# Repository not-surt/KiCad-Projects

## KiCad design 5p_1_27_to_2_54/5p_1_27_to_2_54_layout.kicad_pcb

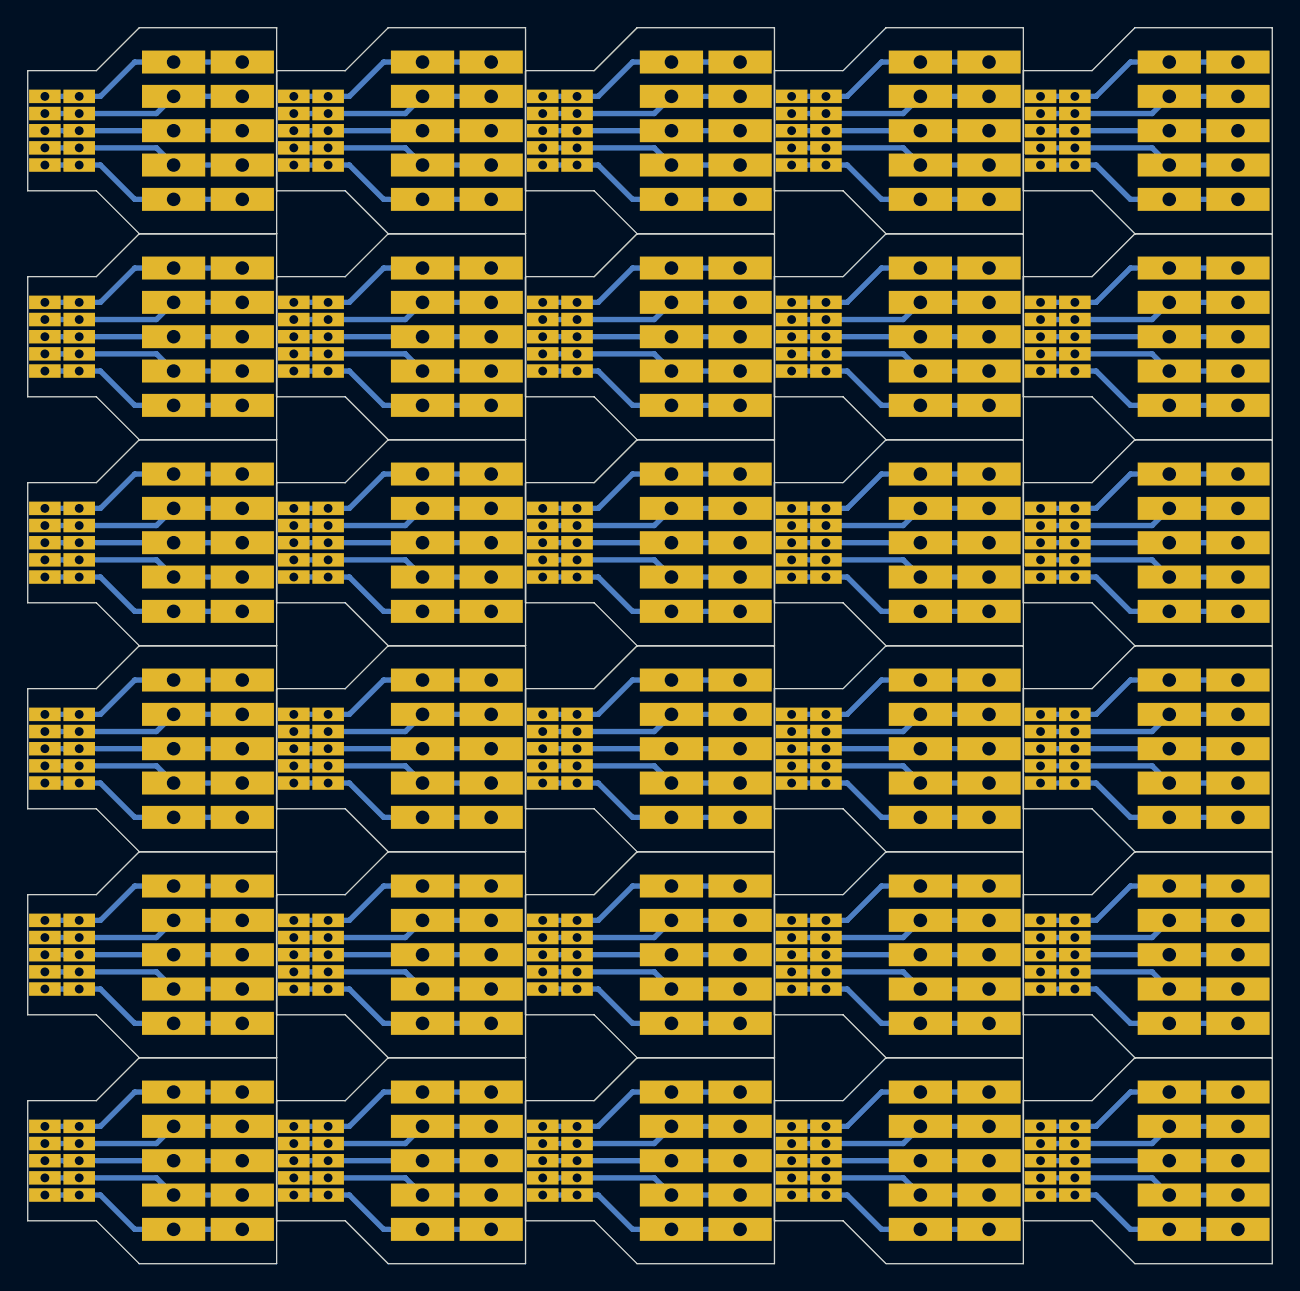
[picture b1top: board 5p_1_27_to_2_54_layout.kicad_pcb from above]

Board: 2 copper layers, 92.1 x 91.4 mm, 120 parts (0 on the bottom side), 5 nets.

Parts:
J1, J2, J5, J6, J9, J10, J13, J14, J17, J18, J21, J22, J25, J26, J29, J30, J33, J34, J37, J38, J41, J42, J45, J46, J49, J50, J53, J54, J57, J58, J61, J62, J65, J66, J69, J70, J73, J74, J77, J78, J81, J82, J85, J86, J89, J90, J93, J94, J97, J98, J101, J102, J105, J106, J109, J110, J113, J114, J117, J118: Conn_01x05; PinHeader_1x05_P1.27mm_Vertical_stretch
J3, J4, J7, J8, J11, J12, J15, J16, J19, J20, J23, J24, J27, J28, J31, J32, J35, J36, J39, J40, J43, J44, J47, J48, J51, J52, J55, J56, J59, J60, J63, J64, J67, J68, J71, J72, J75, J76, J79, J80, J83, J84, J87, J88, J91, J92, J95, J96, J99, J100, J103, J104, J107, J108, J111, J112, J115, J116, J119, J120: Conn_01x05; PinHeader_1x05_P2.54mm_Vertical_stretch

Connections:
unnamed: J1.1, J2.1, J3.1, J4.1, J5.1, J6.1, J7.1, J8.1, J9.1, J10.1, J11.1, J12.1, J13.1, J14.1, J15.1, J16.1, J17.1, J18.1, J19.1, J20.1, J21.1, J22.1, J23.1, J24.1, J25.1, J26.1, J27.1, J28.1, J29.1, J30.1, J31.1, J32.1, J33.1, J34.1, J35.1, J36.1, J37.1, J38.1, J39.1, J40.1, J41.1, J42.1, J43.1, J44.1, J45.1, J46.1, J47.1, J48.1, J49.1, J50.1, J51.1, J52.1, J53.1, J54.1, J55.1, J56.1, J57.1, J58.1, J59.1, J60.1, J61.1, J62.1, J63.1, J64.1, J65.1, J66.1, J67.1, J68.1, J69.1, J70.1, J71.1, J72.1, J73.1, J74.1, J75.1, J76.1, J77.1, J78.1, J79.1, J80.1, J81.1, J82.1, J83.1, J84.1, J85.1, J86.1, J87.1, J88.1, J89.1, J90.1, J91.1, J92.1, J93.1, J94.1, J95.1, J96.1, J97.1, J98.1, J99.1, J100.1, J101.1, J102.1, J103.1, J104.1, J105.1, J106.1, J107.1, J108.1, J109.1, J110.1, J111.1, J112.1, J113.1, J114.1, J115.1, J116.1, J117.1, J118.1, J119.1, J120.1
unnamed: J1.2, J2.2, J3.2, J4.2, J5.2, J6.2, J7.2, J8.2, J9.2, J10.2, J11.2, J12.2, J13.2, J14.2, J15.2, J16.2, J17.2, J18.2, J19.2, J20.2, J21.2, J22.2, J23.2, J24.2, J25.2, J26.2, J27.2, J28.2, J29.2, J30.2, J31.2, J32.2, J33.2, J34.2, J35.2, J36.2, J37.2, J38.2, J39.2, J40.2, J41.2, J42.2, J43.2, J44.2, J45.2, J46.2, J47.2, J48.2, J49.2, J50.2, J51.2, J52.2, J53.2, J54.2, J55.2, J56.2, J57.2, J58.2, J59.2, J60.2, J61.2, J62.2, J63.2, J64.2, J65.2, J66.2, J67.2, J68.2, J69.2, J70.2, J71.2, J72.2, J73.2, J74.2, J75.2, J76.2, J77.2, J78.2, J79.2, J80.2, J81.2, J82.2, J83.2, J84.2, J85.2, J86.2, J87.2, J88.2, J89.2, J90.2, J91.2, J92.2, J93.2, J94.2, J95.2, J96.2, J97.2, J98.2, J99.2, J100.2, J101.2, J102.2, J103.2, J104.2, J105.2, J106.2, J107.2, J108.2, J109.2, J110.2, J111.2, J112.2, J113.2, J114.2, J115.2, J116.2, J117.2, J118.2, J119.2, J120.2
unnamed: J1.3, J2.3, J3.3, J4.3, J5.3, J6.3, J7.3, J8.3, J9.3, J10.3, J11.3, J12.3, J13.3, J14.3, J15.3, J16.3, J17.3, J18.3, J19.3, J20.3, J21.3, J22.3, J23.3, J24.3, J25.3, J26.3, J27.3, J28.3, J29.3, J30.3, J31.3, J32.3, J33.3, J34.3, J35.3, J36.3, J37.3, J38.3, J39.3, J40.3, J41.3, J42.3, J43.3, J44.3, J45.3, J46.3, J47.3, J48.3, J49.3, J50.3, J51.3, J52.3, J53.3, J54.3, J55.3, J56.3, J57.3, J58.3, J59.3, J60.3, J61.3, J62.3, J63.3, J64.3, J65.3, J66.3, J67.3, J68.3, J69.3, J70.3, J71.3, J72.3, J73.3, J74.3, J75.3, J76.3, J77.3, J78.3, J79.3, J80.3, J81.3, J82.3, J83.3, J84.3, J85.3, J86.3, J87.3, J88.3, J89.3, J90.3, J91.3, J92.3, J93.3, J94.3, J95.3, J96.3, J97.3, J98.3, J99.3, J100.3, J101.3, J102.3, J103.3, J104.3, J105.3, J106.3, J107.3, J108.3, J109.3, J110.3, J111.3, J112.3, J113.3, J114.3, J115.3, J116.3, J117.3, J118.3, J119.3, J120.3
unnamed: J1.4, J2.4, J3.4, J4.4, J5.4, J6.4, J7.4, J8.4, J9.4, J10.4, J11.4, J12.4, J13.4, J14.4, J15.4, J16.4, J17.4, J18.4, J19.4, J20.4, J21.4, J22.4, J23.4, J24.4, J25.4, J26.4, J27.4, J28.4, J29.4, J30.4, J31.4, J32.4, J33.4, J34.4, J35.4, J36.4, J37.4, J38.4, J39.4, J40.4, J41.4, J42.4, J43.4, J44.4, J45.4, J46.4, J47.4, J48.4, J49.4, J50.4, J51.4, J52.4, J53.4, J54.4, J55.4, J56.4, J57.4, J58.4, J59.4, J60.4, J61.4, J62.4, J63.4, J64.4, J65.4, J66.4, J67.4, J68.4, J69.4, J70.4, J71.4, J72.4, J73.4, J74.4, J75.4, J76.4, J77.4, J78.4, J79.4, J80.4, J81.4, J82.4, J83.4, J84.4, J85.4, J86.4, J87.4, J88.4, J89.4, J90.4, J91.4, J92.4, J93.4, J94.4, J95.4, J96.4, J97.4, J98.4, J99.4, J100.4, J101.4, J102.4, J103.4, J104.4, J105.4, J106.4, J107.4, J108.4, J109.4, J110.4, J111.4, J112.4, J113.4, J114.4, J115.4, J116.4, J117.4, J118.4, J119.4, J120.4
unnamed: J1.5, J2.5, J3.5, J4.5, J5.5, J6.5, J7.5, J8.5, J9.5, J10.5, J11.5, J12.5, J13.5, J14.5, J15.5, J16.5, J17.5, J18.5, J19.5, J20.5, J21.5, J22.5, J23.5, J24.5, J25.5, J26.5, J27.5, J28.5, J29.5, J30.5, J31.5, J32.5, J33.5, J34.5, J35.5, J36.5, J37.5, J38.5, J39.5, J40.5, J41.5, J42.5, J43.5, J44.5, J45.5, J46.5, J47.5, J48.5, J49.5, J50.5, J51.5, J52.5, J53.5, J54.5, J55.5, J56.5, J57.5, J58.5, J59.5, J60.5, J61.5, J62.5, J63.5, J64.5, J65.5, J66.5, J67.5, J68.5, J69.5, J70.5, J71.5, J72.5, J73.5, J74.5, J75.5, J76.5, J77.5, J78.5, J79.5, J80.5, J81.5, J82.5, J83.5, J84.5, J85.5, J86.5, J87.5, J88.5, J89.5, J90.5, J91.5, J92.5, J93.5, J94.5, J95.5, J96.5, J97.5, J98.5, J99.5, J100.5, J101.5, J102.5, J103.5, J104.5, J105.5, J106.5, J107.5, J108.5, J109.5, J110.5, J111.5, J112.5, J113.5, J114.5, J115.5, J116.5, J117.5, J118.5, J119.5, J120.5

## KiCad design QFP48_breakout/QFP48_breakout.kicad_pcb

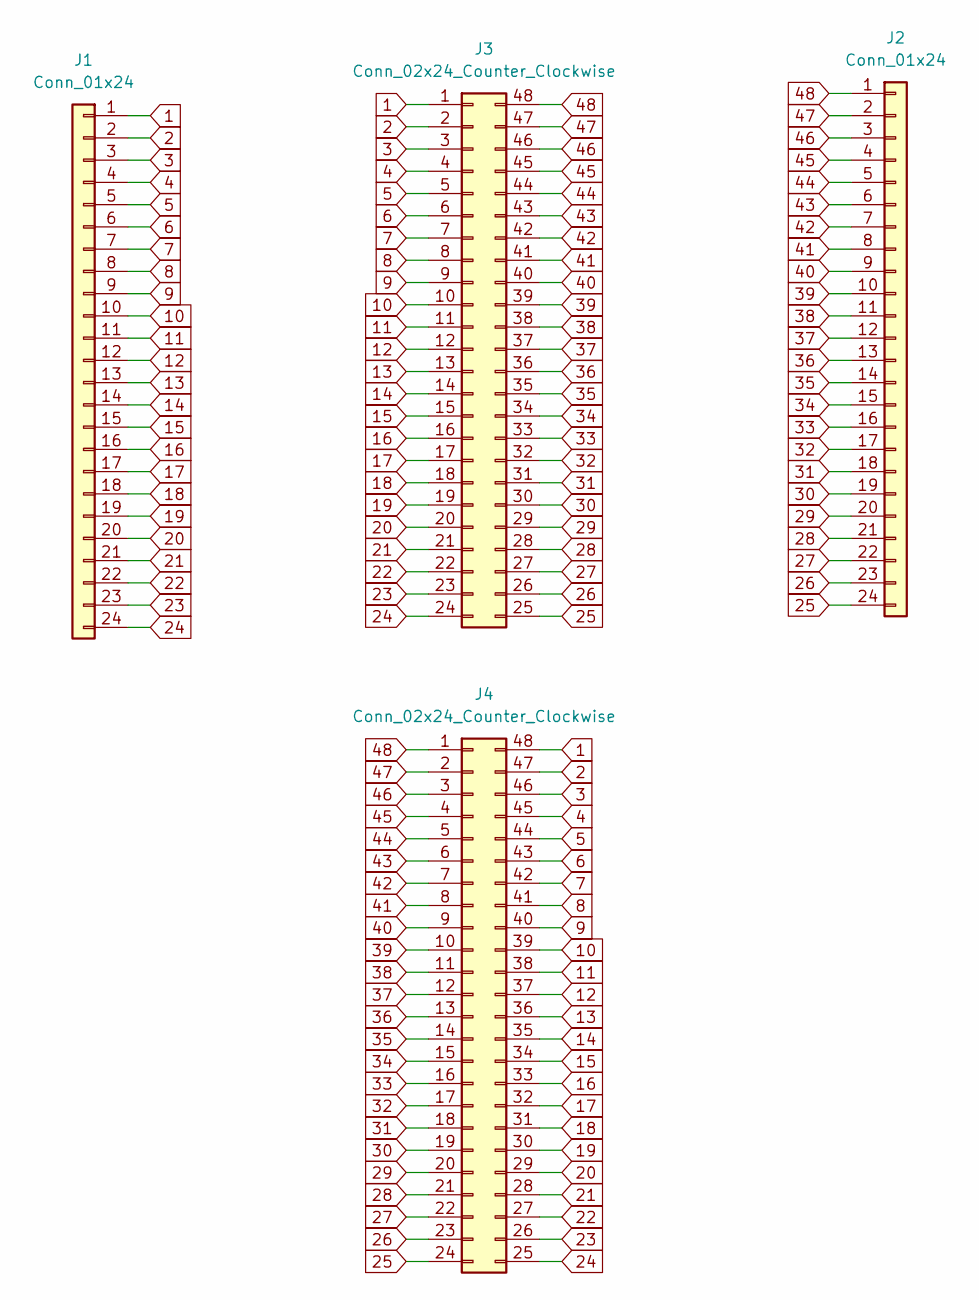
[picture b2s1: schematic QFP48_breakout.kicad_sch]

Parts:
J1, J2: Conn_01x24; PinHeader_1x24_P2.54mm_Vertical_no_silk
J3: Conn_02x24_Counter_Clockwise; LQFP-48-1EP_7x7mm_P0.5mm_EP3.6x3.6mm
J4: Conn_02x24_Counter_Clockwise; QFN-48-1EP_7x7mm_P0.5mm_EP5.15x5.15mm

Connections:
1: J1.1, J3.1, J4.48
2: J1.2, J3.2, J4.47
3: J1.3, J3.3, J4.46
4: J1.4, J3.4, J4.45
5: J1.5, J3.5, J4.44
6: J1.6, J3.6, J4.43
7: J1.7, J3.7, J4.42
8: J1.8, J3.8, J4.41
9: J1.9, J3.9, J4.40
10: J1.10, J3.10, J4.39
11: J1.11, J3.11, J4.38
12: J1.12, J3.12, J4.37
13: J1.13, J3.13, J4.36
14: J1.14, J3.14, J4.35
15: J1.15, J3.15, J4.34
16: J1.16, J3.16, J4.33
17: J1.17, J3.17, J4.32
18: J1.18, J3.18, J4.31
19: J1.19, J3.19, J4.30
20: J1.20, J3.20, J4.29
21: J1.21, J3.21, J4.28
22: J1.22, J3.22, J4.27
23: J1.23, J3.23, J4.26
24: J1.24, J3.24, J4.25
25: J2.24, J3.25, J4.24
26: J2.23, J3.26, J4.23
27: J2.22, J3.27, J4.22
28: J2.21, J3.28, J4.21
29: J2.20, J3.29, J4.20
30: J2.19, J3.30, J4.19
31: J2.18, J3.31, J4.18
32: J2.17, J3.32, J4.17
33: J2.16, J3.33, J4.16
34: J2.15, J3.34, J4.15
35: J2.14, J3.35, J4.14
36: J2.13, J3.36, J4.13
37: J2.12, J3.37, J4.12
38: J2.11, J3.38, J4.11
39: J2.10, J3.39, J4.10
40: J2.9, J3.40, J4.9
41: J2.8, J3.41, J4.8
42: J2.7, J3.42, J4.7
43: J2.6, J3.43, J4.6
44: J2.5, J3.44, J4.5
45: J2.4, J3.45, J4.4
46: J2.3, J3.46, J4.3
47: J2.2, J3.47, J4.2
48: J2.1, J3.48, J4.1

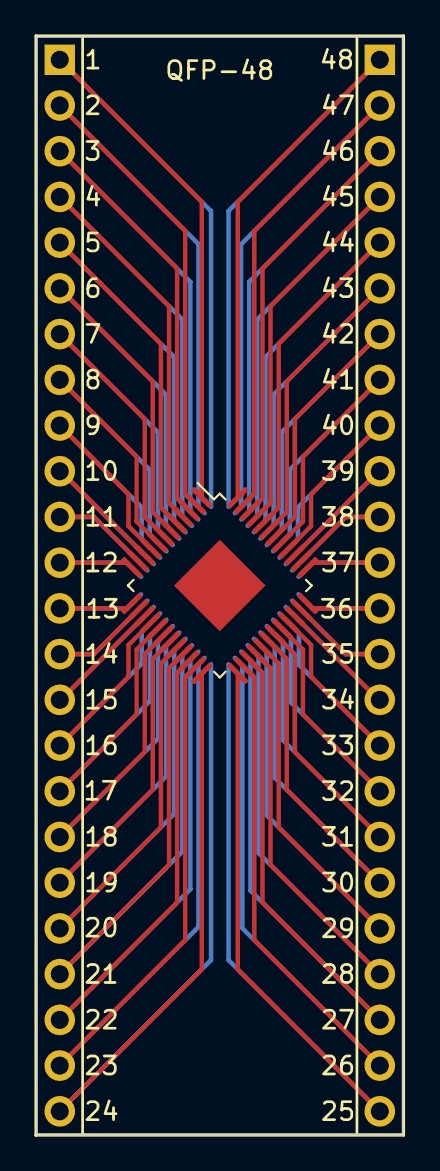
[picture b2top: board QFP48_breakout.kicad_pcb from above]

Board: 2 copper layers, 20.3 x 61.0 mm, 4 parts (1 on the bottom side), 48 nets.

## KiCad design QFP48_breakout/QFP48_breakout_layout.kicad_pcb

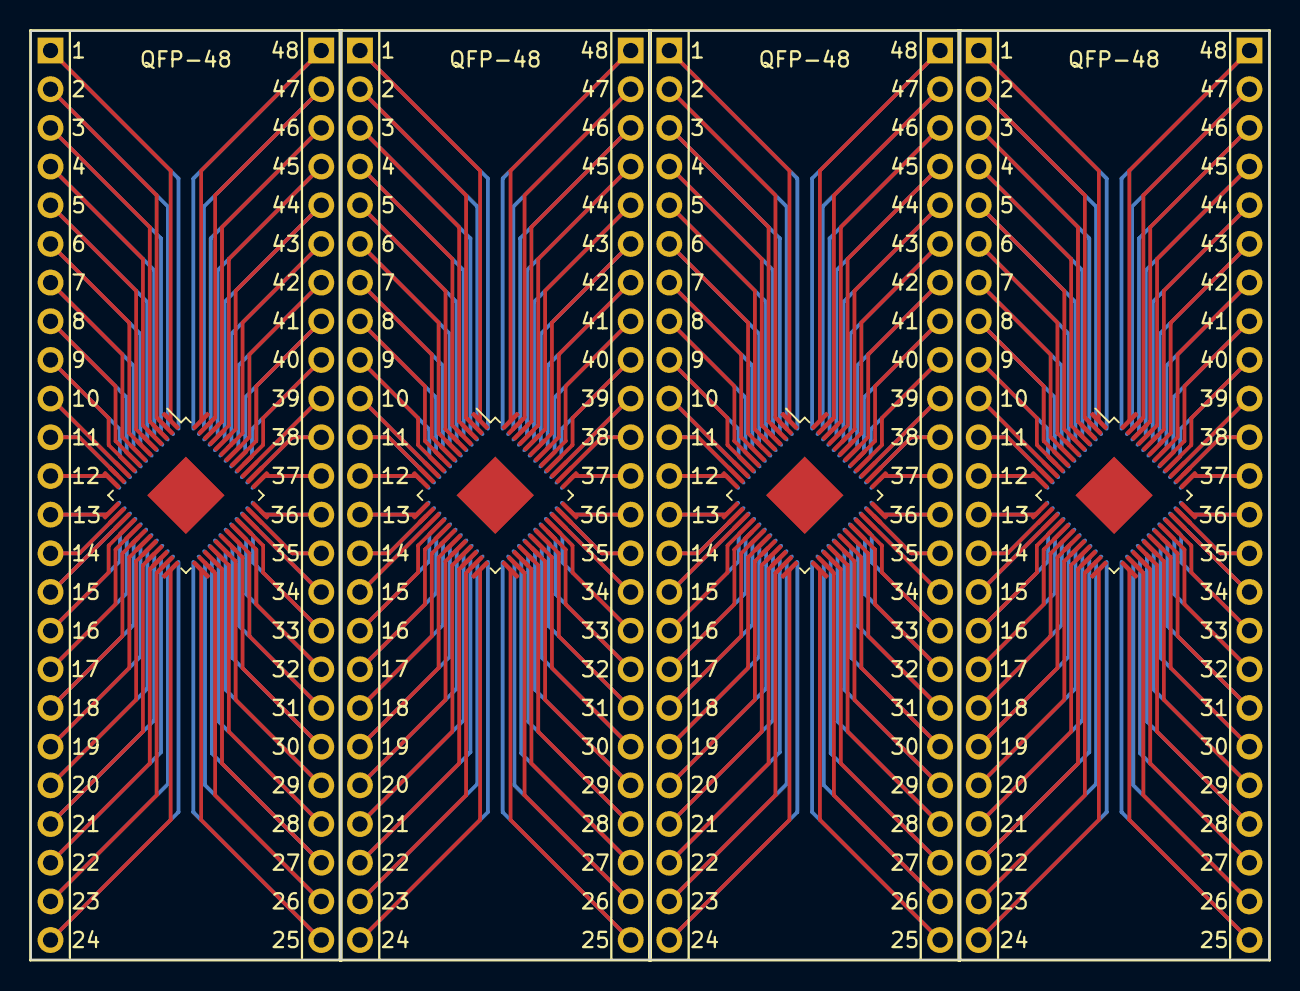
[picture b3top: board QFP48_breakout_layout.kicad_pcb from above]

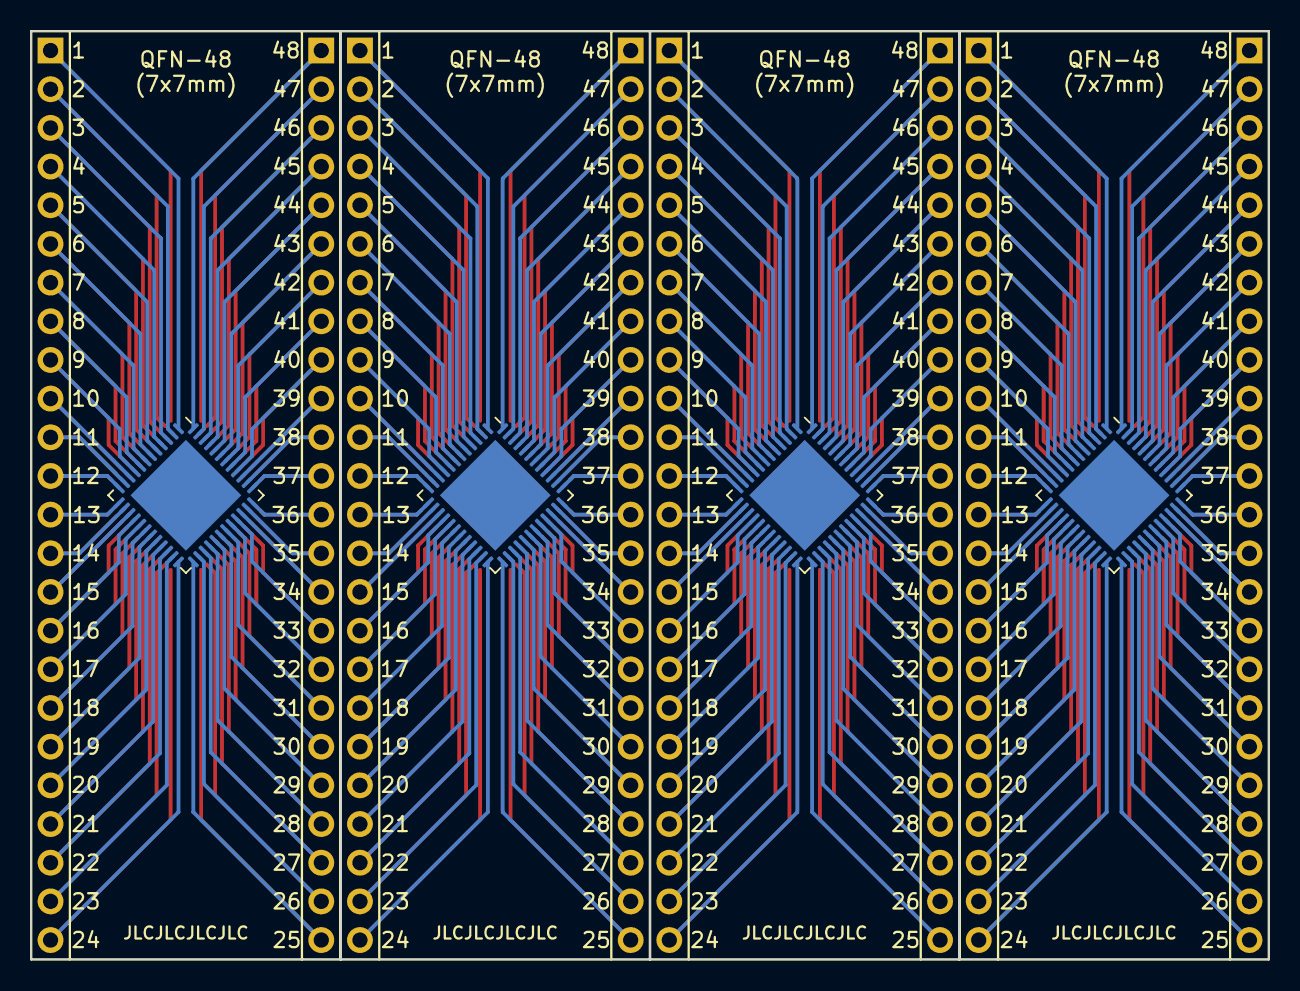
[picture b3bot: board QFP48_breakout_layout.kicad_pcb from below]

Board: 2 copper layers, 81.3 x 61.0 mm, 16 parts (4 on the bottom side), 48 nets.

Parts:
J1, J2, J5, J6, J9, J10, J13, J14: Conn_01x24; PinHeader_1x24_P2.54mm_Vertical_no_silk
J3, J7, J11, J15: Conn_02x24_Counter_Clockwise; LQFP-48-1EP_7x7mm_P0.5mm_EP3.6x3.6mm
J4, J8, J12, J16: Conn_02x24_Counter_Clockwise; QFN-48-1EP_7x7mm_P0.5mm_EP5.15x5.15mm

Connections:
1: J1.1, J3.1, J4.48, J5.1, J7.1, J8.48, J9.1, J11.1, J12.48, J13.1, J15.1, J16.48
2: J1.2, J3.2, J4.47, J5.2, J7.2, J8.47, J9.2, J11.2, J12.47, J13.2, J15.2, J16.47
3: J1.3, J3.3, J4.46, J5.3, J7.3, J8.46, J9.3, J11.3, J12.46, J13.3, J15.3, J16.46
4: J1.4, J3.4, J4.45, J5.4, J7.4, J8.45, J9.4, J11.4, J12.45, J13.4, J15.4, J16.45
5: J1.5, J3.5, J4.44, J5.5, J7.5, J8.44, J9.5, J11.5, J12.44, J13.5, J15.5, J16.44
6: J1.6, J3.6, J4.43, J5.6, J7.6, J8.43, J9.6, J11.6, J12.43, J13.6, J15.6, J16.43
7: J1.7, J3.7, J4.42, J5.7, J7.7, J8.42, J9.7, J11.7, J12.42, J13.7, J15.7, J16.42
8: J1.8, J3.8, J4.41, J5.8, J7.8, J8.41, J9.8, J11.8, J12.41, J13.8, J15.8, J16.41
9: J1.9, J3.9, J4.40, J5.9, J7.9, J8.40, J9.9, J11.9, J12.40, J13.9, J15.9, J16.40
10: J1.10, J3.10, J4.39, J5.10, J7.10, J8.39, J9.10, J11.10, J12.39, J13.10, J15.10, J16.39
11: J1.11, J3.11, J4.38, J5.11, J7.11, J8.38, J9.11, J11.11, J12.38, J13.11, J15.11, J16.38
12: J1.12, J3.12, J4.37, J5.12, J7.12, J8.37, J9.12, J11.12, J12.37, J13.12, J15.12, J16.37
13: J1.13, J3.13, J4.36, J5.13, J7.13, J8.36, J9.13, J11.13, J12.36, J13.13, J15.13, J16.36
14: J1.14, J3.14, J4.35, J5.14, J7.14, J8.35, J9.14, J11.14, J12.35, J13.14, J15.14, J16.35
15: J1.15, J3.15, J4.34, J5.15, J7.15, J8.34, J9.15, J11.15, J12.34, J13.15, J15.15, J16.34
16: J1.16, J3.16, J4.33, J5.16, J7.16, J8.33, J9.16, J11.16, J12.33, J13.16, J15.16, J16.33
17: J1.17, J3.17, J4.32, J5.17, J7.17, J8.32, J9.17, J11.17, J12.32, J13.17, J15.17, J16.32
18: J1.18, J3.18, J4.31, J5.18, J7.18, J8.31, J9.18, J11.18, J12.31, J13.18, J15.18, J16.31
19: J1.19, J3.19, J4.30, J5.19, J7.19, J8.30, J9.19, J11.19, J12.30, J13.19, J15.19, J16.30
20: J1.20, J3.20, J4.29, J5.20, J7.20, J8.29, J9.20, J11.20, J12.29, J13.20, J15.20, J16.29
21: J1.21, J3.21, J4.28, J5.21, J7.21, J8.28, J9.21, J11.21, J12.28, J13.21, J15.21, J16.28
22: J1.22, J3.22, J4.27, J5.22, J7.22, J8.27, J9.22, J11.22, J12.27, J13.22, J15.22, J16.27
23: J1.23, J3.23, J4.26, J5.23, J7.23, J8.26, J9.23, J11.23, J12.26, J13.23, J15.23, J16.26
24: J1.24, J3.24, J4.25, J5.24, J7.24, J8.25, J9.24, J11.24, J12.25, J13.24, J15.24, J16.25
25: J2.24, J3.25, J4.24, J6.24, J7.25, J8.24, J10.24, J11.25, J12.24, J14.24, J15.25, J16.24
26: J2.23, J3.26, J4.23, J6.23, J7.26, J8.23, J10.23, J11.26, J12.23, J14.23, J15.26, J16.23
27: J2.22, J3.27, J4.22, J6.22, J7.27, J8.22, J10.22, J11.27, J12.22, J14.22, J15.27, J16.22
28: J2.21, J3.28, J4.21, J6.21, J7.28, J8.21, J10.21, J11.28, J12.21, J14.21, J15.28, J16.21
29: J2.20, J3.29, J4.20, J6.20, J7.29, J8.20, J10.20, J11.29, J12.20, J14.20, J15.29, J16.20
30: J2.19, J3.30, J4.19, J6.19, J7.30, J8.19, J10.19, J11.30, J12.19, J14.19, J15.30, J16.19
31: J2.18, J3.31, J4.18, J6.18, J7.31, J8.18, J10.18, J11.31, J12.18, J14.18, J15.31, J16.18
32: J2.17, J3.32, J4.17, J6.17, J7.32, J8.17, J10.17, J11.32, J12.17, J14.17, J15.32, J16.17
33: J2.16, J3.33, J4.16, J6.16, J7.33, J8.16, J10.16, J11.33, J12.16, J14.16, J15.33, J16.16
34: J2.15, J3.34, J4.15, J6.15, J7.34, J8.15, J10.15, J11.34, J12.15, J14.15, J15.34, J16.15
35: J2.14, J3.35, J4.14, J6.14, J7.35, J8.14, J10.14, J11.35, J12.14, J14.14, J15.35, J16.14
36: J2.13, J3.36, J4.13, J6.13, J7.36, J8.13, J10.13, J11.36, J12.13, J14.13, J15.36, J16.13
37: J2.12, J3.37, J4.12, J6.12, J7.37, J8.12, J10.12, J11.37, J12.12, J14.12, J15.37, J16.12
38: J2.11, J3.38, J4.11, J6.11, J7.38, J8.11, J10.11, J11.38, J12.11, J14.11, J15.38, J16.11
39: J2.10, J3.39, J4.10, J6.10, J7.39, J8.10, J10.10, J11.39, J12.10, J14.10, J15.39, J16.10
40: J2.9, J3.40, J4.9, J6.9, J7.40, J8.9, J10.9, J11.40, J12.9, J14.9, J15.40, J16.9
41: J2.8, J3.41, J4.8, J6.8, J7.41, J8.8, J10.8, J11.41, J12.8, J14.8, J15.41, J16.8
42: J2.7, J3.42, J4.7, J6.7, J7.42, J8.7, J10.7, J11.42, J12.7, J14.7, J15.42, J16.7
43: J2.6, J3.43, J4.6, J6.6, J7.43, J8.6, J10.6, J11.43, J12.6, J14.6, J15.43, J16.6
44: J2.5, J3.44, J4.5, J6.5, J7.44, J8.5, J10.5, J11.44, J12.5, J14.5, J15.44, J16.5
45: J2.4, J3.45, J4.4, J6.4, J7.45, J8.4, J10.4, J11.45, J12.4, J14.4, J15.45, J16.4
46: J2.3, J3.46, J4.3, J6.3, J7.46, J8.3, J10.3, J11.46, J12.3, J14.3, J15.46, J16.3
47: J2.2, J3.47, J4.2, J6.2, J7.47, J8.2, J10.2, J11.47, J12.2, J14.2, J15.47, J16.2
48: J2.1, J3.48, J4.1, J6.1, J7.48, J8.1, J10.1, J11.48, J12.1, J14.1, J15.48, J16.1
